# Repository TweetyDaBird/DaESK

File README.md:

# DaESK - Dual axis Ergonomic Split Keyboard
 
 Copyright 2020 Markus Knutsson <markus.knutsson@tweety.se>
 
 Licensed under CERN-OHL-S v2 or any later version.

 DaESK is designed as an Ortholinear split keyboard with a detached thumb-key cluster, allowing a different angle/level of tent and positioning for the two parts.

 Key design features:
 * Full SMD design with onboard Atmega32u4 MCU compatible with QMK/TMK and other firmware suites.
 * Onboard IS31FL3737 RGB controller for full per-key adressable RGB matrix with built in effects.
 * Cherry MX type keyswitches in Kaihl Hot-Swap sockets.
 * Mid-mounted USB-C connector for durability and low profile.
 * Dual sided reversible design, identical PCB and thumbcluster PCB for both halves.
 * Each half can work as a master/slave pair (TRRS/I2C link) and as a one-hand gamepad without reprogramming.
 * Flexible thumbcluster design, supports 1-8 keys per side, connected to main PCB with ribbon cable.
 
 Available main layouts:
 * DaESK-4R a ~60%, 4-Row (4x6 key) layout with 48 keys plus 2-16 key thumbcluster for a total of 50-64 keys.
 * DaESK-3R a ~40%, 3-Row (3x6 key) layout with 36 keys plus 2-16 key thumbcluster for a total of 38-52 keys.
 
 Available Thumbcluster layouts:
 * DaESK-TH1 an adaptable ErgoDox style thumbcluster with break-away parts.
 
 Planned features:
 * Already designed in mounting holes for a low profile FR4 midplate/backplate case design.
 * Multiple thumbcluster designs.
 
 Current Version:
 v0.9x - Almost ready for prototype PCB order
 
 ToDo:
 * DaESK-3R, USB-C
 * BOM
 * Silkscreen

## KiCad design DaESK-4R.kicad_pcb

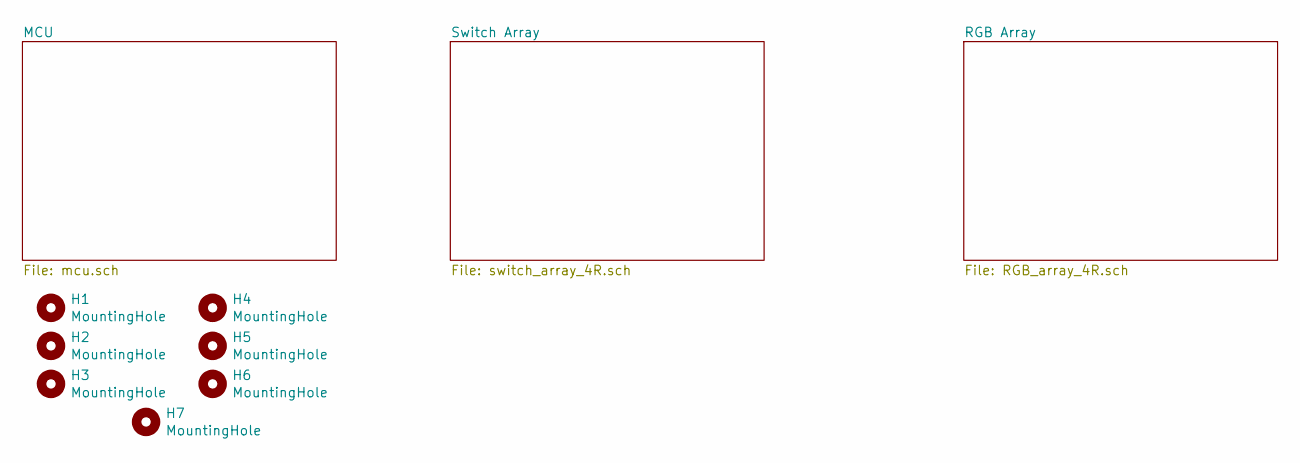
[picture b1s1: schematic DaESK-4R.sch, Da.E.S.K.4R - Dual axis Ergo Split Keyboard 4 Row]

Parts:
H1, H2, H3, H4, H5, H6: MountingHole; MountingHole_3.7mm; Manufacturer_Part_Number Hole
H7: MountingHole; MountingHole_2.2mm_M2; Manufacturer_Part_Number Hole

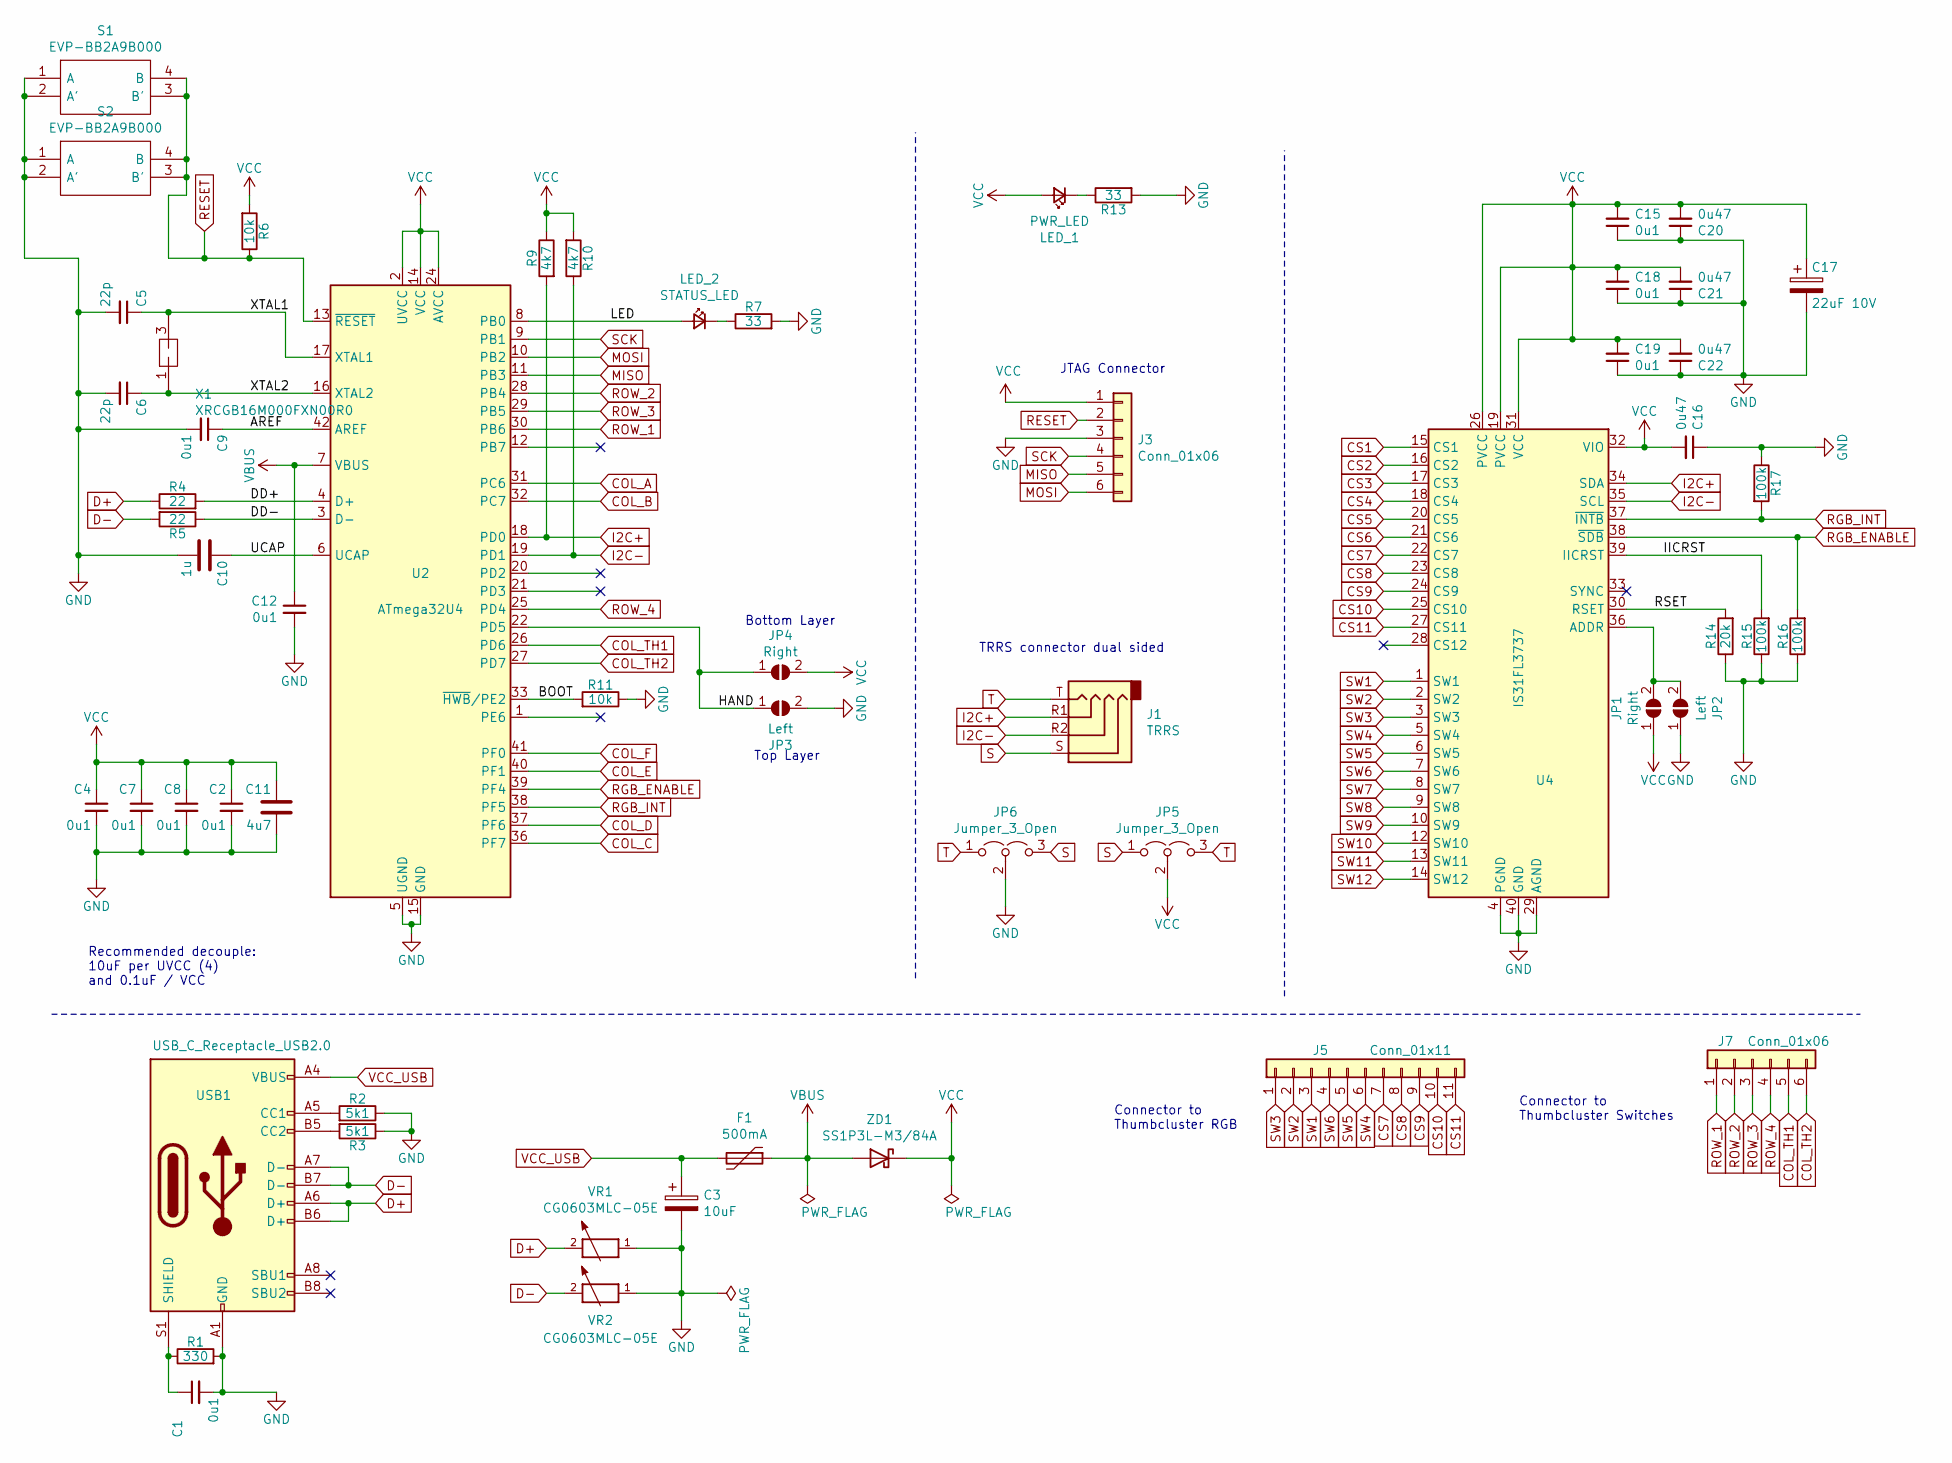
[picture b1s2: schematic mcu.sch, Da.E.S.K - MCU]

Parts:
C1, C2, C4, C7, C8, C9, C12, C15, C18, C19: 0u1; C_0603_1608Metric; Manufacturer_Part_Number 06035C104JAT2A; Mouser Part Number 581-06035C104JAT2A
C3: 10uF; CP_EIA-3216-18_Kemet-A; Manufacturer_Part_Number TAJA106M010RNJ; Mouser Part Number 581-TAJA106M010R
C5, C6: 22p; C_0603_1608Metric; Manufacturer_Part_Number 06035A220JAT2A; Mouser Part Number 581-06035A220J
C10: 1u; C_0805_2012Metric; Manufacturer_Part_Number CL21B105KBFNNNG; Mouser Part Number 187-CL21B105KBFNNNG
C11: 4u7; C_0805_2012Metric; Manufacturer_Part_Number C2012X7R1H475K125AC; Mouser Part Number 810-C2012X7R475K125C
C16, C20, C21, C22: 0u47; C_0603_1608Metric; Manufacturer_Part_Number UMK107B7474KA-TR; Mouser Part Number 963-UMK107B7474KA-TR
C17: 22uF 10V; CP_EIA-3216-18_Kemet-A; Manufacturer_Part_Number TPSA226K010T0900; Mouser Part Number 581-TPSA226K010T0900
F1: 500mA; Fuse_0603_1608Metric; Manufacturer_Part_Number 04000025WR; Mouser Part Number 576-04000025WR
J1: TRRS; TRRS-PJ-320A-reversible; Manufacturer_Part_Number PJ-320A
J3: Conn_01x06; PinHeader_2x03_P1.27mm_Vertical; Manufacturer_Part_Number Pinheader
J5: Conn_01x11; PinHeader_1x11_P1.27mm_Vertical; Manufacturer_Part_Number Pinheader
J7: Conn_01x06; PinHeader_1x06_P1.27mm_Vertical; Manufacturer_Part_Number Pinheader
JP1, JP4: Right; SolderJumper-2_P1.3mm_Open_TrianglePad1.0x1.5mm; Manufacturer_Part_Number Jumper
JP2, JP3: Left; SolderJumper-2_P1.3mm_Open_TrianglePad1.0x1.5mm; Manufacturer_Part_Number Jumper
JP5, JP6: Jumper_3_Open; SolderJumper-3_P1.3mm_Bridged12_RoundedPad1.0x1.5mm_NumberL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; Manufacturer_Part_Number Jumper
LED_1: PWR_LED; LED_0603_1608Metric; Manufacturer_Part_Number APT1608EC; Mouser Part Number 604-APT1608EC
LED_2: STATUS_LED; LED_0603_1608Metric; Manufacturer_Part_Number APT1608EC; Mouser Part Number 604-APT1608EC
R1: 330; R_0603_1608Metric; Manufacturer_Part_Number ERJ-3EKF3300V; Mouser Part Number 667-ERJ-3EKF3300V
R2, R3: 5k1; R_0603_1608Metric; Manufacturer_Part_Number ERJ-3EKF5101V; Mouser Part Number 667-ERJ-3EKF5101V
R4, R5: 22; R_0603_1608Metric; Manufacturer_Part_Number ERJ-3GEYJ220V; Mouser Part Number 667-ERJ-3GEYJ220V
R6, R11: 10k; R_0603_1608Metric; Manufacturer_Part_Number ERJ-3EKF1002V; Mouser Part Number 667-ERJ-3GEYJ103V
R7, R13: 33; R_0603_1608Metric; Manufacturer_Part_Number ERJ-3EKF33R0V; Mouser Part Number 667-ERJ-3EKF33R0V
R9, R10: 4k7; R_0603_1608Metric; Manufacturer_Part_Number ERJ-3GEYJ472V; Mouser Part Number 667-ERJ-3GEYJ472V
R14: 20k; R_0603_1608Metric; Manufacturer_Part_Number ERJ-3GEYJ203V; Mouser Part Number 667-ERJ-3GEYJ203V
R15, R16, R17: 100k; R_0603_1608Metric; Manufacturer_Part_Number ERJ-3EKF1003V; Mouser Part Number 667-ERJ-3EKF1003V
S1, S2: EVP-BB2A9B000; EVPBB2A9B000; Mouser Part Number 667-EVP-BB2A9B000
U2: ATmega32U4; QFN-44-1EP_7x7mm_P0.5mm_EP5.15x5.15mm_ThermalVias; Manufacturer_Part_Number ATMEGA32U4RC-MU; Mouser Part Number 556-ATMEGA32U4RC-MU
U4: IS31FL3737; QFN-40-1EP_5x5mm_P0.4mm_EP3.8x3.8mm_ThermalVias; Mouser Part Number 870-IS31FL3733-TQLS4
USB1: USB_C_Receptacle_USB2.0; HRO-TYPE-C-31-M-14; Manufacturer_Part_Number HRO-TYPE-C-31-M-14
VR1, VR2: CG0603MLC-05E; R_0603_1608Metric; Mouser Part Number 652-CG0603MLC-05E
X1: XRCGB16M000FXN00R0; XRCGB16M000FXN1R0; Mouser Part Number 81-XRCGB16M000FXN00R
ZD1: SS1P3L-M3/84A; 84A; Manufacturer_Part_Number SS1P3L-M3/84A; Mouser Part Number 625-SS1P3L-M3/84A

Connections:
/MCU/AREF: C9.1, U2.42 (AREF)
/MCU/BOOT: R11.2, U2.33 (~HWB~/PE2)
/MCU/DD+: R4.2, U2.4 (D+)
/MCU/DD-: R5.1, U2.3 (D-)
/MCU/HAND: JP3.1 (A), JP4.1 (A), U2.22 (PD5)
/MCU/IICRST: R15.2, U4.39 (IICRST)
/MCU/LED: LED_2.2 (A), U2.8 (PB0)
/MCU/RSET: R14.2, U4.30 (RSET)
/MCU/UCAP: C10.1, U2.6 (UCAP)
/MCU/XTAL1: C5.1, U2.17 (XTAL1), X1.3
/MCU/XTAL2: C6.1, U2.16 (XTAL2), X1.1
COL_A: U2.31 (PC6); also elsewhere on the board
COL_B: U2.32 (PC7); also elsewhere on the board
COL_C: U2.36 (PF7); also elsewhere on the board
COL_D: U2.37 (PF6); also elsewhere on the board
COL_E: U2.40 (PF1); also elsewhere on the board
COL_F: U2.41 (PF0); also elsewhere on the board
COL_TH1: J7.5, U2.26 (PD6)
COL_TH2: J7.6, U2.27 (PD7)
CS1: U4.15 (CS1); also elsewhere on the board
CS2: U4.16 (CS2); also elsewhere on the board
CS3: U4.17 (CS3); also elsewhere on the board
CS4: U4.18 (CS4); also elsewhere on the board
CS5: U4.20 (CS5); also elsewhere on the board
CS6: U4.21 (CS6); also elsewhere on the board
CS7: J5.7, U4.22 (CS7)
CS8: J5.8, U4.23 (CS8)
CS9: J5.9, U4.24 (CS9)
CS10: J5.10, U4.25 (CS10)
CS11: J5.11, U4.27 (CS11)
D+: R4.1, USB1.A6 (D+), USB1.B6 (D+), VR1.2
D-: R5.2, USB1.A7 (D-), USB1.B7 (D-), VR2.2
GND: C1.2, C2.2, C3.2, C4.2, C5.2, C6.2, C7.2, C8.2, C9.2, C10.2, C11.2, C12.2, C15.1, C16.1, C17.2, C18.1, C19.1, C20.1, C21.1, C22.1, J3.3, JP2.1 (A), JP3.2 (B), JP6.2 (C), R1.2, R2.1, R3.1, R7.2, R11.1, R13.2, R14.1, R15.1, R16.1, R17.1, S1.1 (A), S1.2 (A'), S2.1 (A), S2.2 (A'), U2.5 (UGND), U2.15 (GND), U2.23 (GND), U2.35 (GND), U2.43 (GND), U4.4 (PGND), U4.11 (PGND), U4.29 (AGND), U4.40 (GND), U4.41 (GND), USB1.A1 (GND), USB1.A12 (GND), USB1.B1 (GND), USB1.B12 (GND), VR1.1, VR2.1
I2C+: J1.R1, R9.2, U2.18 (PD0), U4.34 (SDA)
I2C-: J1.R2, R10.1, U2.19 (PD1), U4.35 (SCL)
MISO: J3.5, U2.11 (PB3)
MOSI: J3.6, U2.10 (PB2)
unnamed: C1.1, R1.1, USB1.S1 (SHIELD)
unnamed: JP1.2 (B), JP2.2 (B), U4.36 (ADDR)
unnamed: LED_1.1 (K), R13.1
unnamed: LED_2.1 (K), R7.1
unnamed: R2.2, USB1.A5 (CC1)
unnamed: R3.2, USB1.B5 (CC2)
RESET: J3.2, R6.1, S1.3 (B'), S1.4 (B), S2.3 (B'), S2.4 (B), U2.13 (~RESET)
RGB_ENABLE: R16.2, U2.39 (PF4), U4.38 (~SDB)
RGB_INT: R17.2, U2.38 (PF5), U4.37 (~INTB)
ROW_1: J7.1, U2.30 (PB6); also elsewhere on the board
ROW_2: J7.2, U2.28 (PB4); also elsewhere on the board
ROW_3: J7.3, U2.29 (PB5); also elsewhere on the board
ROW_4: J7.4, U2.25 (PD4); also elsewhere on the board
S: J1.S, JP5.1 (A), JP6.3 (B)
SCK: J3.4, U2.9 (PB1)
SW1: J5.3, U4.1 (SW1); also elsewhere on the board
SW2: J5.2, U4.2 (SW2); also elsewhere on the board
SW3: J5.1, U4.3 (SW3); also elsewhere on the board
SW4: J5.6, U4.5 (SW4); also elsewhere on the board
SW5: J5.5, U4.6 (SW5); also elsewhere on the board
SW6: J5.4, U4.7 (SW6); also elsewhere on the board
SW7: U4.8 (SW7); also elsewhere on the board
SW8: U4.9 (SW8); also elsewhere on the board
SW9: U4.10 (SW9); also elsewhere on the board
SW10: U4.12 (SW10); also elsewhere on the board
SW11: U4.13 (SW11); also elsewhere on the board
SW12: U4.14 (SW12); also elsewhere on the board
T: J1.T, JP5.3 (B), JP6.1 (A)
VBUS: C12.1, F1.1, U2.7 (VBUS), ZD1.2 (A)
VCC: C2.1, C4.1, C7.1, C8.1, C11.1, C15.2, C16.2, C17.1, C18.2, C19.2, C20.2, C21.2, C22.2, J3.1, JP1.1 (A), JP4.2 (B), JP5.2 (C), LED_1.2 (A), R6.2, R9.1, R10.2, U2.2 (UVCC), U2.14 (VCC), U2.24 (AVCC), U2.34 (VCC), U2.44 (AVCC), U4.19 (PVCC), U4.26 (PVCC), U4.31 (VCC), U4.32 (VIO), ZD1.1 (K)
VCC_USB: C3.1, F1.2, USB1.A4 (VBUS), USB1.A9 (VBUS), USB1.B4 (VBUS), USB1.B9 (VBUS)

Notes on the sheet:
Recommended decouple: 10uF per UVCC (4) and 0.1uF / VCC
JTAG Connector
Bottom Layer
Top Layer
TRRS connector dual sided
Connector to Thumbcluster Switches
Connector to Thumbcluster RGB

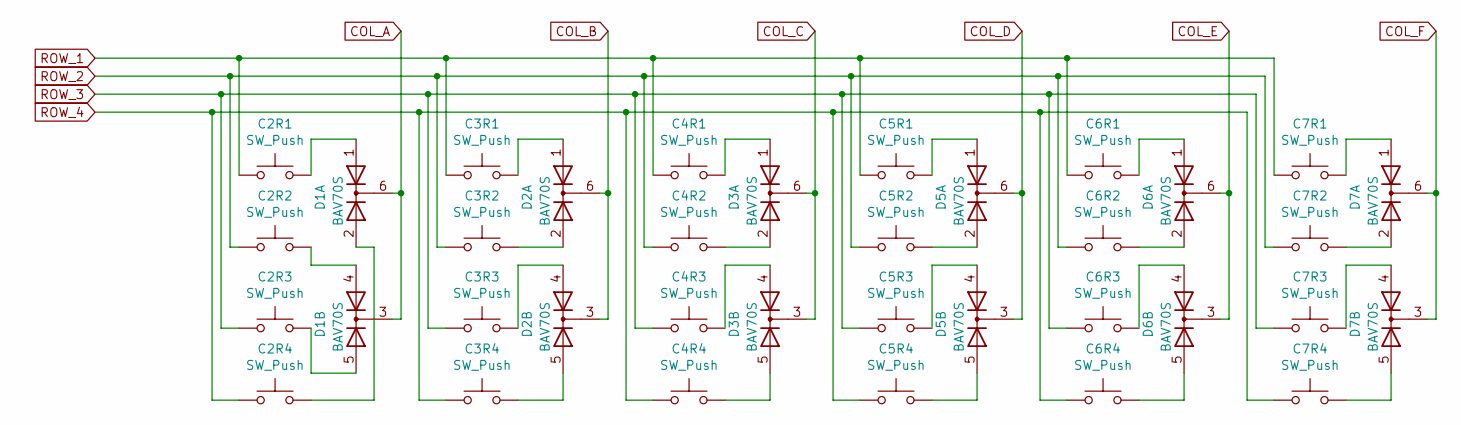
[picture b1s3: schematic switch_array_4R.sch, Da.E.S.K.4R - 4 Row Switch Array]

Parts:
C2R1, C2R2, C2R3, C2R4, C3R1, C3R2, C3R3, C3R4, C4R1, C4R2, C4R3, C4R4, C5R1, C5R2, C5R3, C5R4, C6R1, C6R2, C6R3, C6R4, C7R1, C7R2, C7R3, C7R4: SW_Push; Kailh_socket_MX_reversible_v2; Manufacturer_Part_Number CPG151101S11
D1, D2, D3, D5, D6, D7: BAV70S; SOT-363_SC-70-6; Manufacturer_Part_Number BAV70S,135; Mouser Part Number 771-BAV70S135

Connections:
COL_A: D1.3 (K), D1.6 (K); also elsewhere on the board
COL_B: D2.3 (K), D2.6 (K); also elsewhere on the board
COL_C: D3.3 (K), D3.6 (K); also elsewhere on the board
COL_D: D5.3 (K), D5.6 (K); also elsewhere on the board
COL_E: D6.3 (K), D6.6 (K); also elsewhere on the board
COL_F: D7.3 (K), D7.6 (K); also elsewhere on the board
unnamed: C2R1.2, D1.1 (A)
unnamed: C2R2.2, D1.4 (A)
unnamed: C2R3.2, D1.5 (A)
unnamed: C2R4.2, D1.2 (A)
unnamed: C3R1.2, D2.1 (A)
unnamed: C3R2.2, D2.2 (A)
unnamed: C3R3.2, D2.4 (A)
unnamed: C3R4.2, D2.5 (A)
unnamed: C4R1.2, D3.1 (A)
unnamed: C4R2.2, D3.2 (A)
unnamed: C4R3.2, D3.4 (A)
unnamed: C4R4.2, D3.5 (A)
unnamed: C5R1.2, D5.1 (A)
unnamed: C5R2.2, D5.2 (A)
unnamed: C5R3.2, D5.4 (A)
unnamed: C5R4.2, D5.5 (A)
unnamed: C6R1.2, D6.1 (A)
unnamed: C6R2.2, D6.2 (A)
unnamed: C6R3.2, D6.4 (A)
unnamed: C6R4.2, D6.5 (A)
unnamed: C7R1.2, D7.1 (A)
unnamed: C7R2.2, D7.2 (A)
unnamed: C7R3.2, D7.4 (A)
unnamed: C7R4.2, D7.5 (A)
ROW_1: C2R1.1, C3R1.1, C4R1.1, C5R1.1, C6R1.1, C7R1.1; also elsewhere on the board
ROW_2: C2R2.1, C3R2.1, C4R2.1, C5R2.1, C6R2.1, C7R2.1; also elsewhere on the board
ROW_3: C2R3.1, C3R3.1, C4R3.1, C5R3.1, C6R3.1, C7R3.1; also elsewhere on the board
ROW_4: C2R4.1, C3R4.1, C4R4.1, C5R4.1, C6R4.1, C7R4.1; also elsewhere on the board

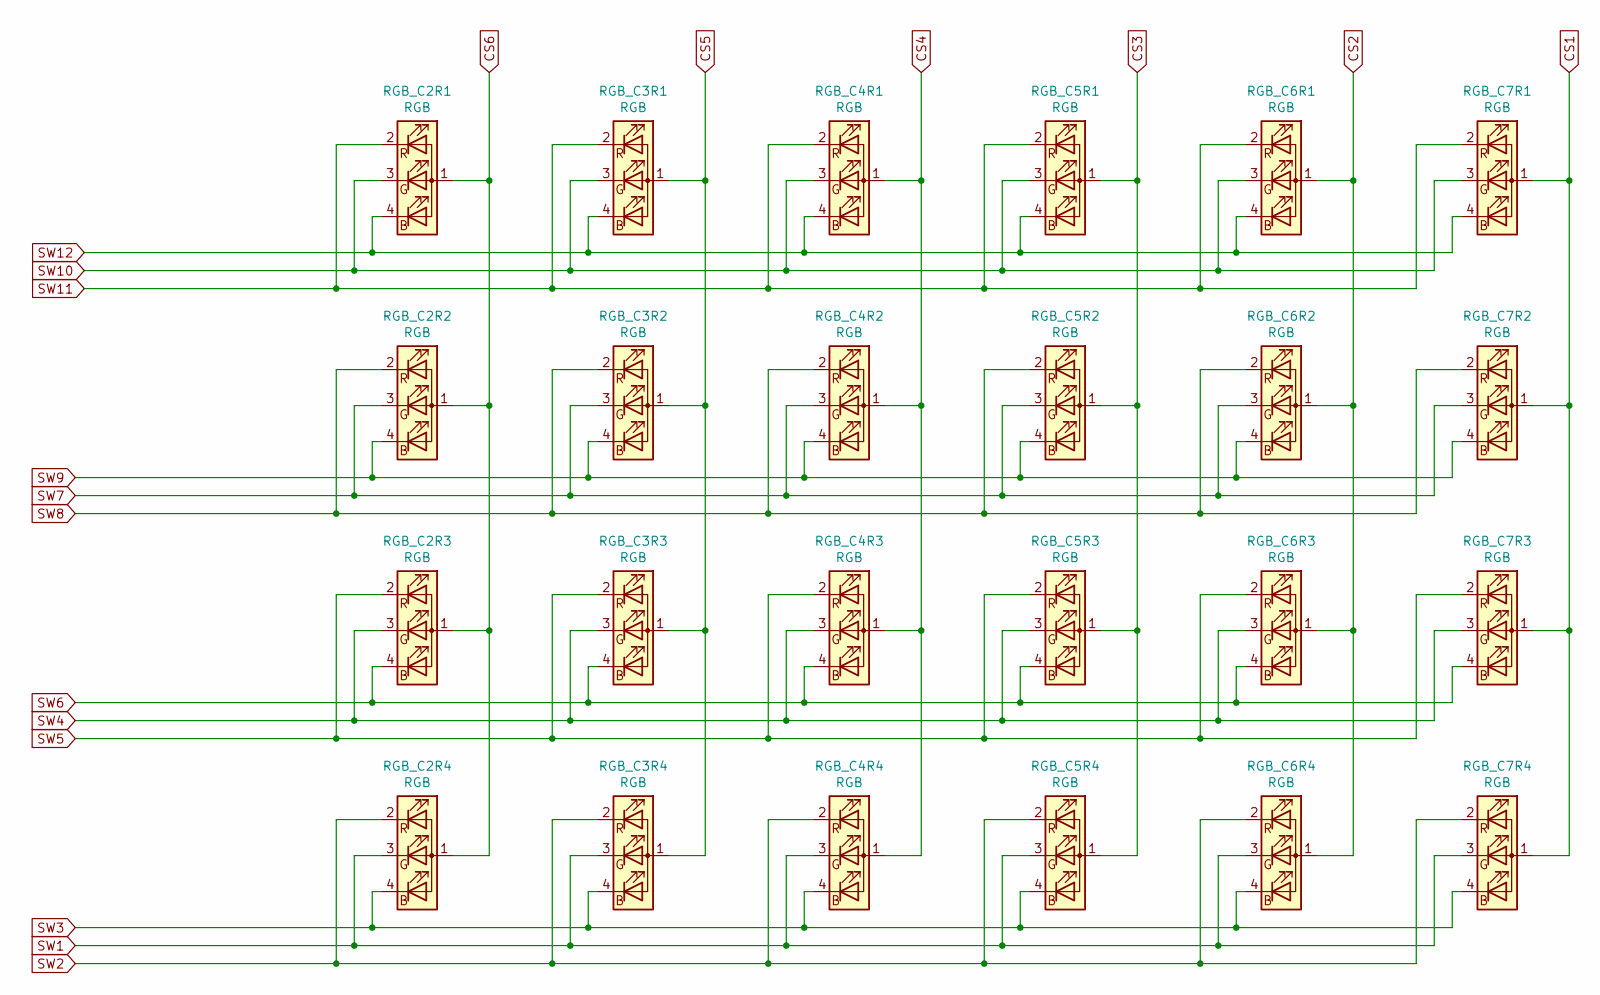
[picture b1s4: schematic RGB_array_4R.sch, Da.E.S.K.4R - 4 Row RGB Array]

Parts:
RGB_C2R1, RGB_C2R2, RGB_C2R3, RGB_C2R4, RGB_C3R1, RGB_C3R2, RGB_C3R3, RGB_C3R4, RGB_C4R1, RGB_C4R2, RGB_C4R3, RGB_C4R4, RGB_C5R1, RGB_C5R2, RGB_C5R3, RGB_C5R4, RGB_C6R1, RGB_C6R2, RGB_C6R3, RGB_C6R4, RGB_C7R1, RGB_C7R2, RGB_C7R3, RGB_C7R4: RGB; LEDSC160X160X070-4N_reversible; Mouser Part Number 604-APTF1616SEJ3ZGGV

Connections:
CS1: RGB_C7R1.1 (A), RGB_C7R2.1 (A), RGB_C7R3.1 (A), RGB_C7R4.1 (A); also elsewhere on the board
CS2: RGB_C6R1.1 (A), RGB_C6R2.1 (A), RGB_C6R3.1 (A), RGB_C6R4.1 (A); also elsewhere on the board
CS3: RGB_C5R1.1 (A), RGB_C5R2.1 (A), RGB_C5R3.1 (A), RGB_C5R4.1 (A); also elsewhere on the board
CS4: RGB_C4R1.1 (A), RGB_C4R2.1 (A), RGB_C4R3.1 (A), RGB_C4R4.1 (A); also elsewhere on the board
CS5: RGB_C3R1.1 (A), RGB_C3R2.1 (A), RGB_C3R3.1 (A), RGB_C3R4.1 (A); also elsewhere on the board
CS6: RGB_C2R1.1 (A), RGB_C2R2.1 (A), RGB_C2R3.1 (A), RGB_C2R4.1 (A); also elsewhere on the board
SW1: RGB_C2R4.3 (GK), RGB_C3R4.3 (GK), RGB_C4R4.3 (GK), RGB_C5R4.3 (GK), RGB_C6R4.3 (GK), RGB_C7R4.3 (GK); also elsewhere on the board
SW2: RGB_C2R4.2 (RK), RGB_C3R4.2 (RK), RGB_C4R4.2 (RK), RGB_C5R4.2 (RK), RGB_C6R4.2 (RK), RGB_C7R4.2 (RK); also elsewhere on the board
SW3: RGB_C2R4.4 (BK), RGB_C3R4.4 (BK), RGB_C4R4.4 (BK), RGB_C5R4.4 (BK), RGB_C6R4.4 (BK), RGB_C7R4.4 (BK); also elsewhere on the board
SW4: RGB_C2R3.3 (GK), RGB_C3R3.3 (GK), RGB_C4R3.3 (GK), RGB_C5R3.3 (GK), RGB_C6R3.3 (GK), RGB_C7R3.3 (GK); also elsewhere on the board
SW5: RGB_C2R3.2 (RK), RGB_C3R3.2 (RK), RGB_C4R3.2 (RK), RGB_C5R3.2 (RK), RGB_C6R3.2 (RK), RGB_C7R3.2 (RK); also elsewhere on the board
SW6: RGB_C2R3.4 (BK), RGB_C3R3.4 (BK), RGB_C4R3.4 (BK), RGB_C5R3.4 (BK), RGB_C6R3.4 (BK), RGB_C7R3.4 (BK); also elsewhere on the board
SW7: RGB_C2R2.3 (GK), RGB_C3R2.3 (GK), RGB_C4R2.3 (GK), RGB_C5R2.3 (GK), RGB_C6R2.3 (GK), RGB_C7R2.3 (GK); also elsewhere on the board
SW8: RGB_C2R2.2 (RK), RGB_C3R2.2 (RK), RGB_C4R2.2 (RK), RGB_C5R2.2 (RK), RGB_C6R2.2 (RK), RGB_C7R2.2 (RK); also elsewhere on the board
SW9: RGB_C2R2.4 (BK), RGB_C3R2.4 (BK), RGB_C4R2.4 (BK), RGB_C5R2.4 (BK), RGB_C6R2.4 (BK), RGB_C7R2.4 (BK); also elsewhere on the board
SW10: RGB_C2R1.3 (GK), RGB_C3R1.3 (GK), RGB_C4R1.3 (GK), RGB_C5R1.3 (GK), RGB_C6R1.3 (GK), RGB_C7R1.3 (GK); also elsewhere on the board
SW11: RGB_C2R1.2 (RK), RGB_C3R1.2 (RK), RGB_C4R1.2 (RK), RGB_C5R1.2 (RK), RGB_C6R1.2 (RK), RGB_C7R1.2 (RK); also elsewhere on the board
SW12: RGB_C2R1.4 (BK), RGB_C3R1.4 (BK), RGB_C4R1.4 (BK), RGB_C5R1.4 (BK), RGB_C6R1.4 (BK), RGB_C7R1.4 (BK); also elsewhere on the board

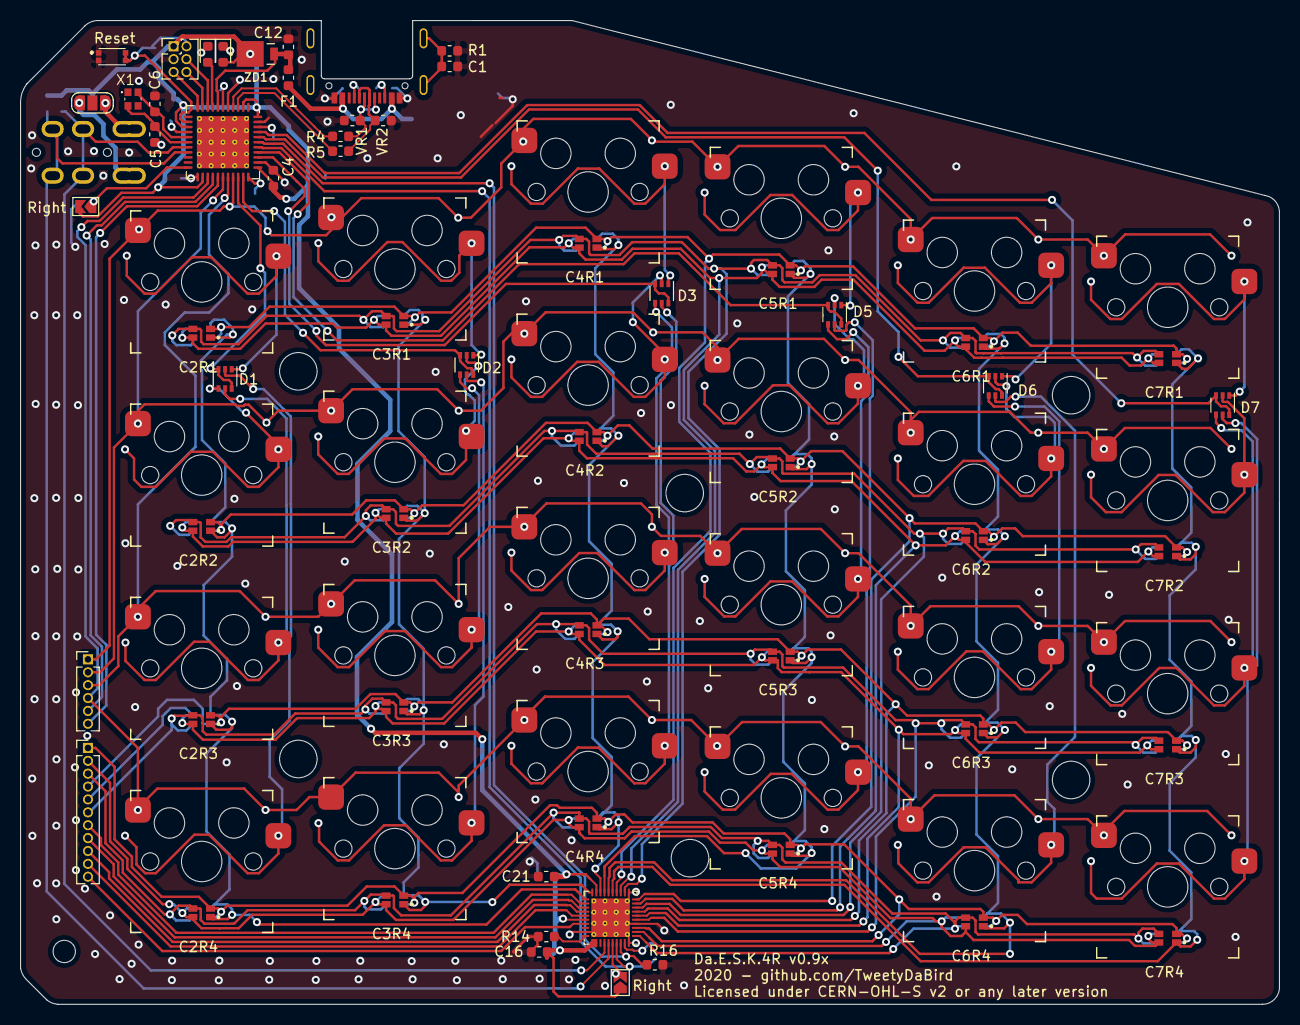
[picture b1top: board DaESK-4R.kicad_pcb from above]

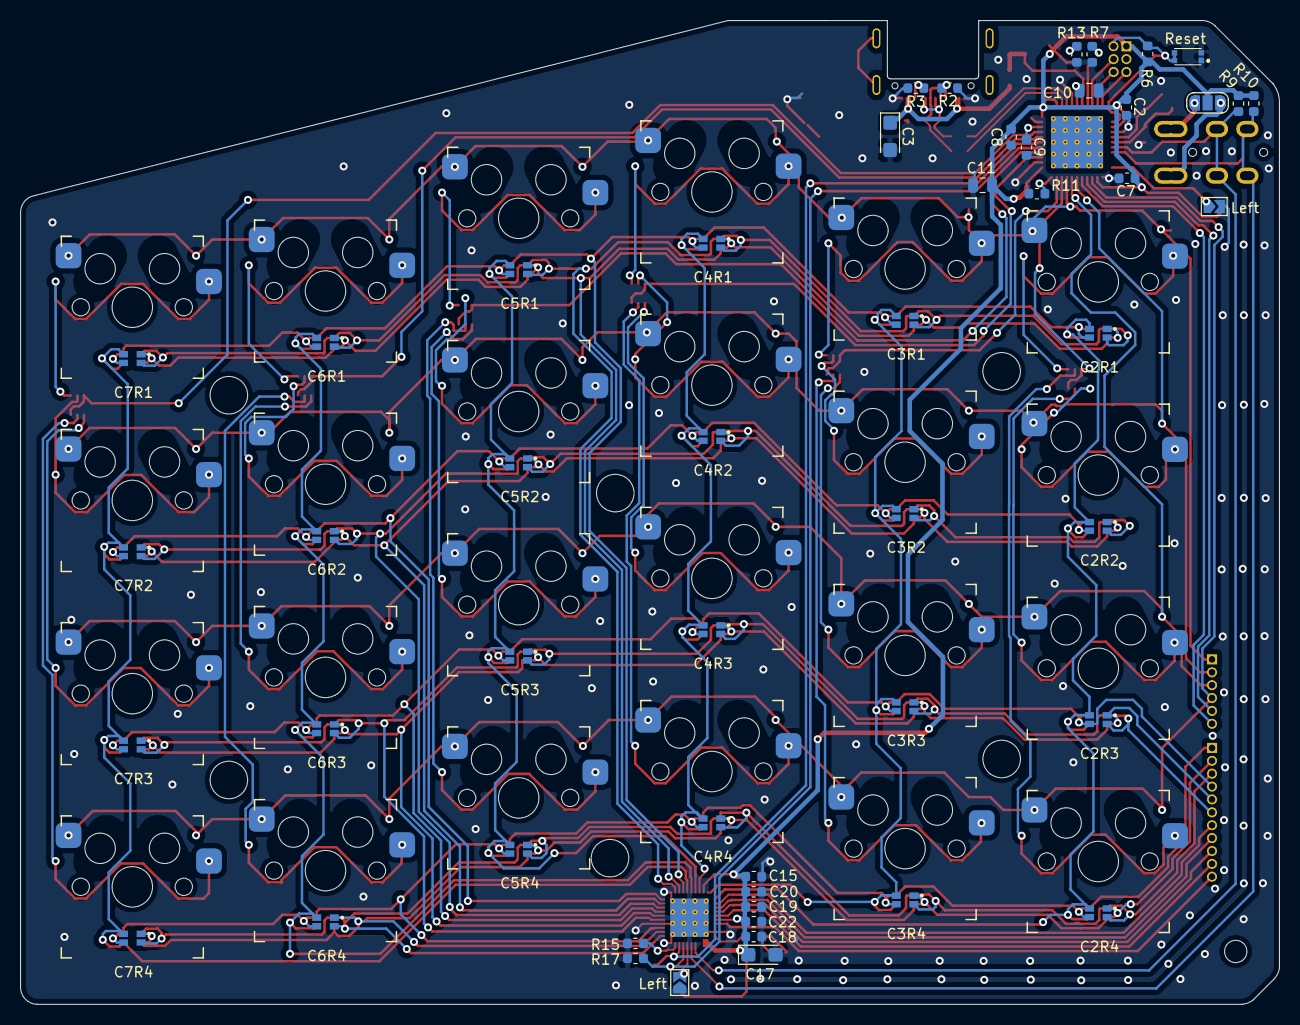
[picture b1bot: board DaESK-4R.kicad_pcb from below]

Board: 2 copper layers, 124.1 x 97.0 mm, 118 parts (27 on the bottom side), 92 nets.

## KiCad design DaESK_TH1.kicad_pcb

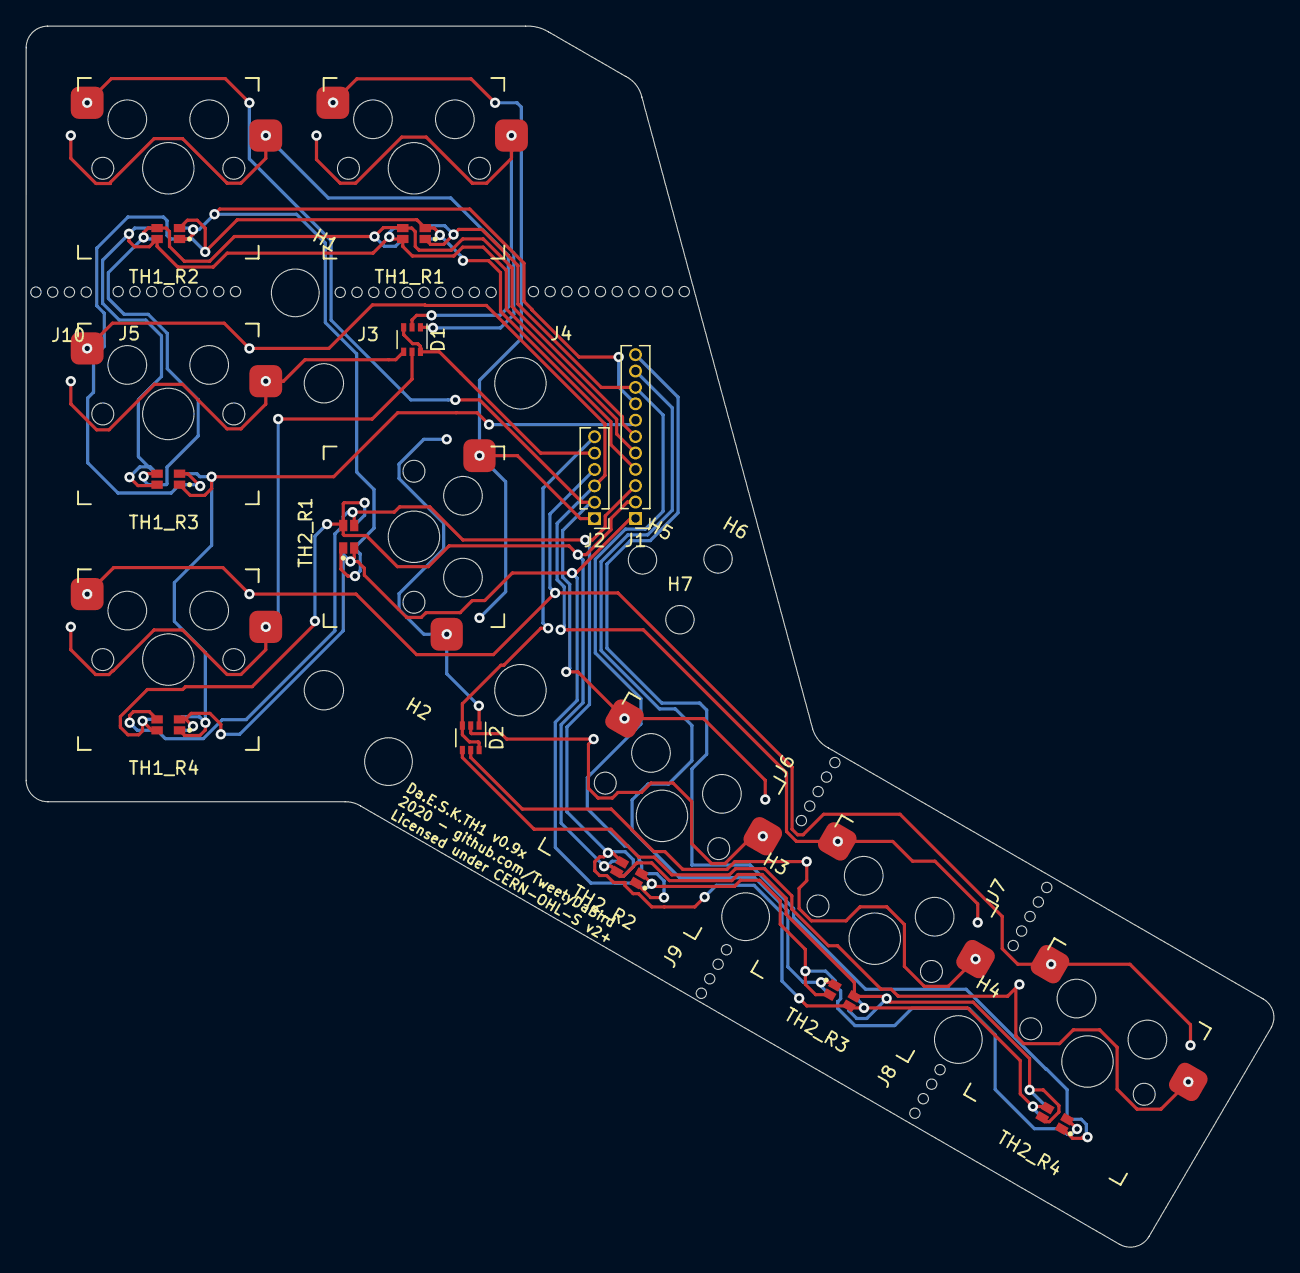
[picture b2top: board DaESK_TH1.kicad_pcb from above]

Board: 2 copper layers, 96.8 x 94.7 mm, 36 parts (0 on the bottom side), 25 nets.

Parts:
D1, D2: BAV70S; SOT-363_SC-70-6
H1, H2, H3, H4: MountingHole; MountingHole_3.7mm
H5, H6, H7: MountingHole; MountingHole_2.2mm_M2_ISO7380
J1: Conn_01x11; PinHeader_1x11_P1.27mm_Vertical
J2: Conn_01x06; PinHeader_1x06_P1.27mm_Vertical
J3, J4: Mousebite 10; mousebite10
J5: Mousebite 8; mousebite8
J6, J7: Mousebite 5; mousebite5
J8, J9, J10: Mousebite 4; mousebite4
RGB_TH1R1: CB1_9; LEDSC160X160X070-4N_reversible
RGB_TH1R2: CB1_8; LEDSC160X160X070-4N_reversible
RGB_TH1R3: CB1_7; LEDSC160X160X070-4N_reversible
RGB_TH1R4: CB1_6; LEDSC160X160X070-4N_reversible
RGB_TH2R1: CB2_1; LEDSC160X160X070-4N_reversible
RGB_TH2R2: CB2_2; LEDSC160X160X070-4N_reversible
RGB_TH2R3, RGB_TH2R4: CB2_3; LEDSC160X160X070-4N_reversible
ST1: stab; Stabilizer_MX_2u
TH1_R1, TH1_R2, TH1_R3, TH1_R4, TH2_R2, TH2_R3, TH2_R4: SW_Push; Kailh_socket_MX_reversible_v2
TH2_R1: SW_Push; Kailh_socket_MX_reversible_v2_2u

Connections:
CS1_TH: J1.7, RGB_TH1R3.1, RGB_TH1R4.1
CS2_TH: J1.8, RGB_TH1R2.1, RGB_TH2R1.1
CS3_TH: J1.9, RGB_TH1R1.1, RGB_TH2R2.1
CS4_TH: J1.10, RGB_TH2R3.1
CS5_TH: J1.11, RGB_TH2R4.1
unnamed: D1.1, TH1_R1.2
unnamed: D1.2, TH1_R2.2
unnamed: D1.4, TH1_R3.2
unnamed: D1.5, TH1_R4.2
unnamed: D2.1, TH2_R1.2
unnamed: D2.2, TH2_R2.2
unnamed: D2.4, TH2_R4.2
unnamed: D2.5, TH2_R3.2
SW1_TH: J1.3, RGB_TH1R4.3, RGB_TH2R1.3, RGB_TH2R2.3, RGB_TH2R3.3, RGB_TH2R4.3
SW2_TH: J1.2, RGB_TH1R4.2, RGB_TH2R1.2, RGB_TH2R2.2, RGB_TH2R3.2, RGB_TH2R4.2
SW3_TH: J1.1, RGB_TH1R4.4, RGB_TH2R1.4, RGB_TH2R2.4, RGB_TH2R3.4, RGB_TH2R4.4
SW4_TH: J1.6, RGB_TH1R1.3, RGB_TH1R2.3, RGB_TH1R3.3
SW5_TH: J1.5, RGB_TH1R1.2, RGB_TH1R2.2, RGB_TH1R3.2
SW6_TH: J1.4, RGB_TH1R1.4, RGB_TH1R2.4, RGB_TH1R3.4
TH_COL_TH1: D1.3, D1.6, J2.5
TH_COL_TH2: D2.3, D2.6, J2.6
TH_ROW_1: J2.1, TH1_R1.1, TH2_R1.1
TH_ROW_2: J2.2, TH1_R2.1, TH2_R2.1
TH_ROW_3: J2.3, TH1_R3.1, TH2_R3.1
TH_ROW_4: J2.4, TH1_R4.1, TH2_R4.1

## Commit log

2020-09-29 main
2020-09-29 initial upload of design
2020-09-29 pcb udated
2020-10-13 4R updated placement of MCU
2020-10-13 fixed reset switch
